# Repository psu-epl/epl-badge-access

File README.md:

# epl-badge-access

This is a mono-repo that contains hardwire designs, software, and documentation for a complete dual-band RFID access control system. This repo represents the work produced by ECE capstone team 17 during the 2021 - 2022 academic year.

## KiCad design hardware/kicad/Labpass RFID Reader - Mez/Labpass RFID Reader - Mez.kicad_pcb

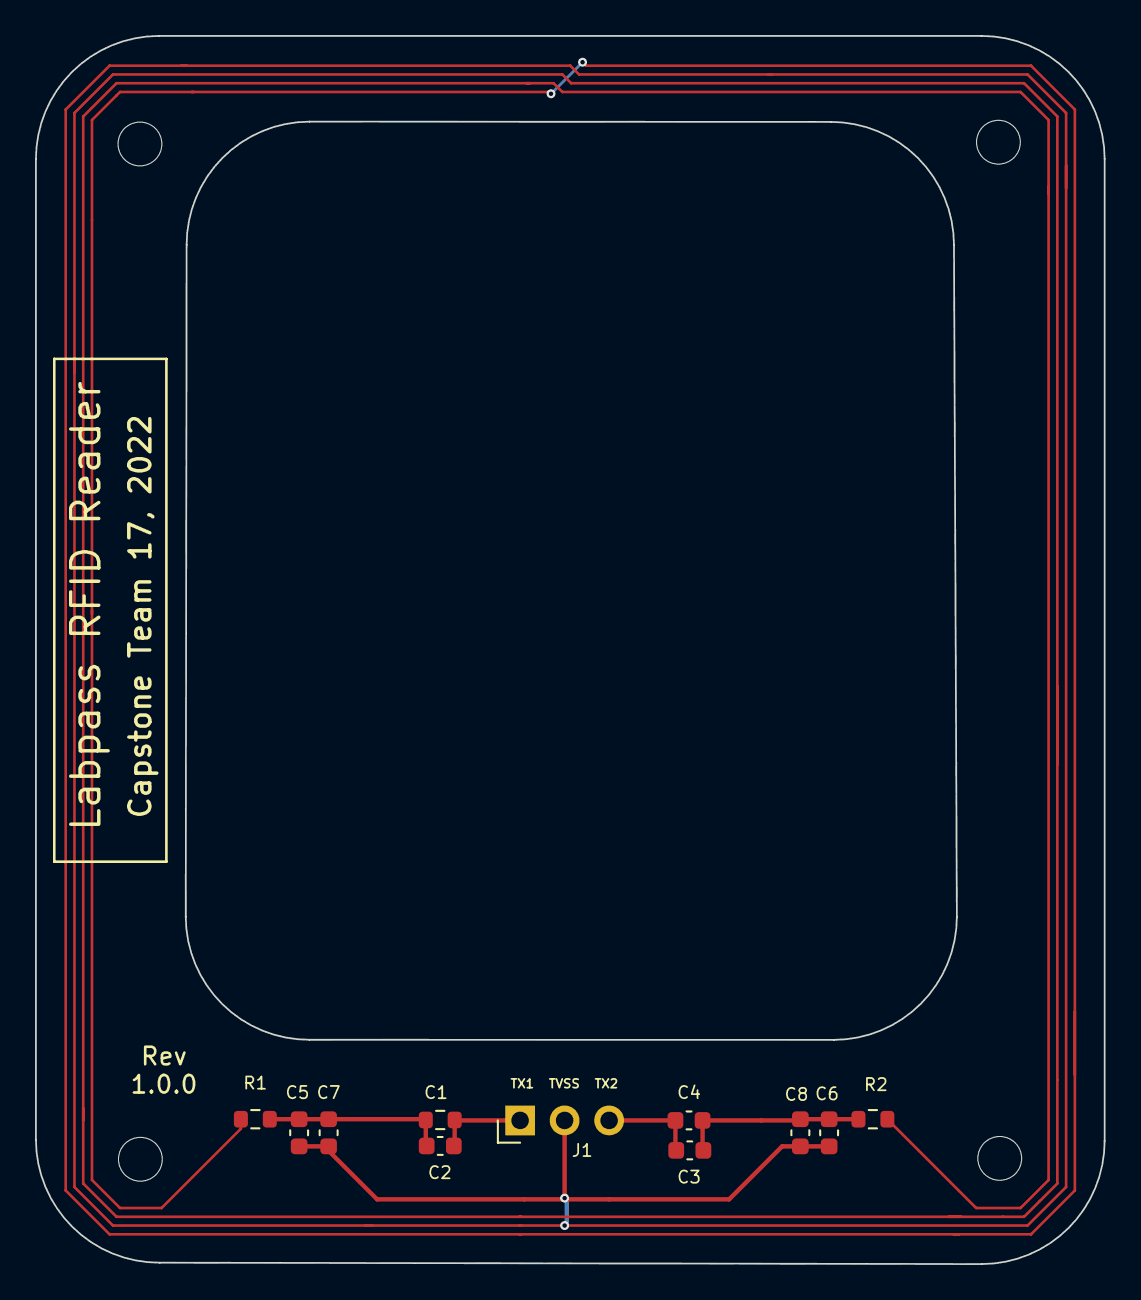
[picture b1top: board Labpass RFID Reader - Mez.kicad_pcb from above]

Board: 2 copper layers, 61.0 x 70.1 mm, 11 parts (0 on the bottom side), 5 nets.

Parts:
C1: 11p; R_0603_1608Metric
C2, C3: NC; C_0603_1608Metric
C4: 11p; C_0603_1608Metric
C5, C6: 30p; C_0603_1608Metric
C7, C8: 32p; C_0603_1608Metric
J1: Conn_01x03_Male; PinHeader_1x03_P2.54mm_Horizontal
R1, R2: R_US; R_0603_1608Metric

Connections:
unnamed: C1.1, C2.1, J1.1
unnamed: C1.2, C2.2, C5.2, C7.1, R1.1
unnamed: C3.1, C4.1, J1.3
unnamed: C3.2, C4.2, C6.1, C8.2, R2.1
unnamed: C5.1, C6.2, C7.2, C8.1, J1.2, R1.2, R2.2

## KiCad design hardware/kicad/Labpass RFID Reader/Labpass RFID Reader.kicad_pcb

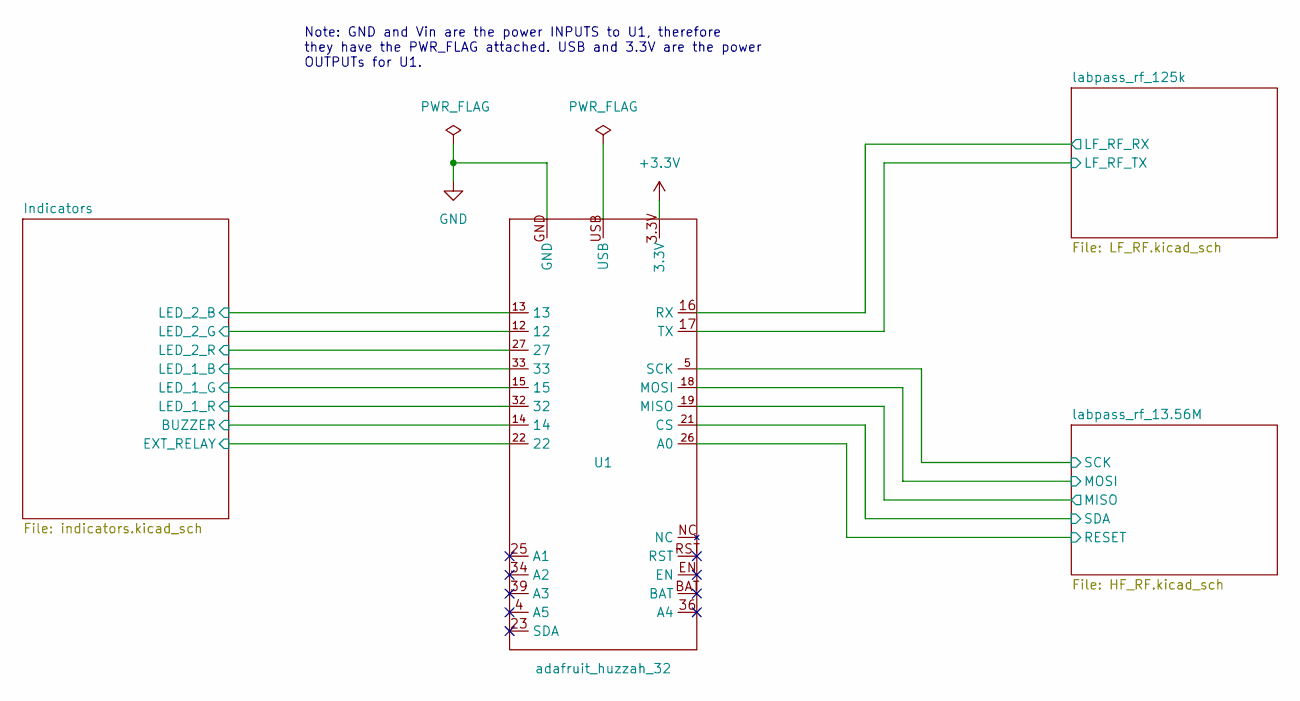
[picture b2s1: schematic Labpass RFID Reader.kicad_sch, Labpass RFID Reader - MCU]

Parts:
U1: adafruit_huzzah_32

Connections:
/Indicators/BUZZER: U1.14; also elsewhere on the board
/Indicators/EXT_RELAY: U1.22; also elsewhere on the board
/Indicators/LED_1_B: U1.33; also elsewhere on the board
/Indicators/LED_1_G: U1.15; also elsewhere on the board
/Indicators/LED_1_R: U1.32; also elsewhere on the board
/Indicators/LED_2_B: U1.13; also elsewhere on the board
/Indicators/LED_2_G: U1.12; also elsewhere on the board
/Indicators/LED_2_R: U1.27; also elsewhere on the board
/labpass_rf_13.56M/MISO: U1.19 (MISO); also elsewhere on the board
/labpass_rf_13.56M/MOSI: U1.18 (MOSI); also elsewhere on the board
/labpass_rf_13.56M/RESET: U1.26 (A0); also elsewhere on the board
/labpass_rf_13.56M/SCK: U1.5 (SCK); also elsewhere on the board
/labpass_rf_13.56M/SDA: U1.21 (CS); also elsewhere on the board
/labpass_rf_125k/LF_RF_RX: U1.16 (RX); also elsewhere on the board
/labpass_rf_125k/LF_RF_TX: U1.17 (TX); also elsewhere on the board

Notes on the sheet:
Note: GND and Vin are the power INPUTS to U1, therefore they have the PWR_FLAG attached. USB and 3.3V are the power OUTPUTs for U1.

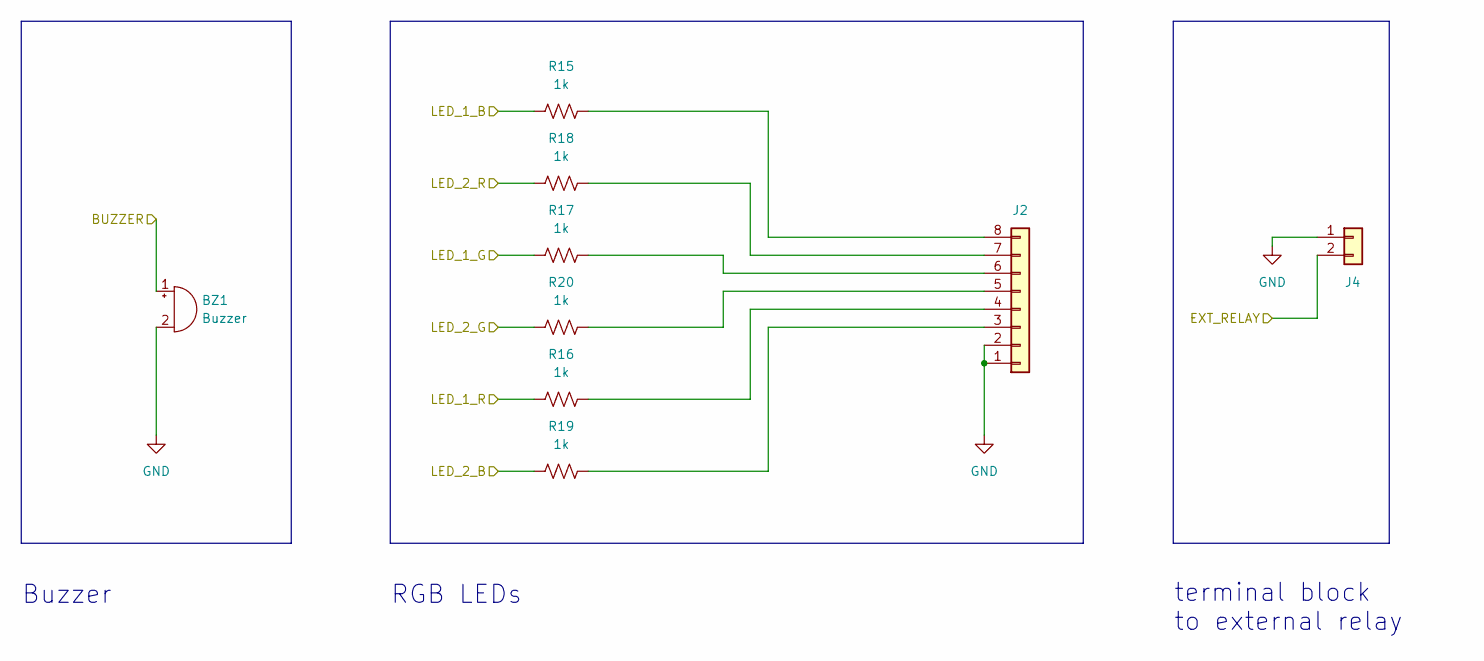
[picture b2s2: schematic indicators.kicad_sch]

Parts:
BZ1: Buzzer; buzzer
J2: Conn_01x08; PinHeader_2x04_P2.54mm_Horizontal
J4: Conn_01x02; Anytek NQ
R15, R16, R17, R18, R19, R20: 1k; R_0603_1608Metric

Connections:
/Indicators/BUZZER: BZ1.1 (-); also elsewhere on the board
/Indicators/EXT_RELAY: J4.2; also elsewhere on the board
/Indicators/LED_1_B: R15.1; also elsewhere on the board
/Indicators/LED_1_G: R17.1; also elsewhere on the board
/Indicators/LED_1_R: R16.1; also elsewhere on the board
/Indicators/LED_2_B: R19.1; also elsewhere on the board
/Indicators/LED_2_G: R20.1; also elsewhere on the board
/Indicators/LED_2_R: R18.1; also elsewhere on the board
unnamed: J2.3, R19.2
unnamed: J2.4, R16.2
unnamed: J2.5, R20.2
unnamed: J2.6, R17.2
unnamed: J2.7, R18.2
unnamed: J2.8, R15.2

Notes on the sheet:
RGB LEDs
terminal block to external relay
Buzzer

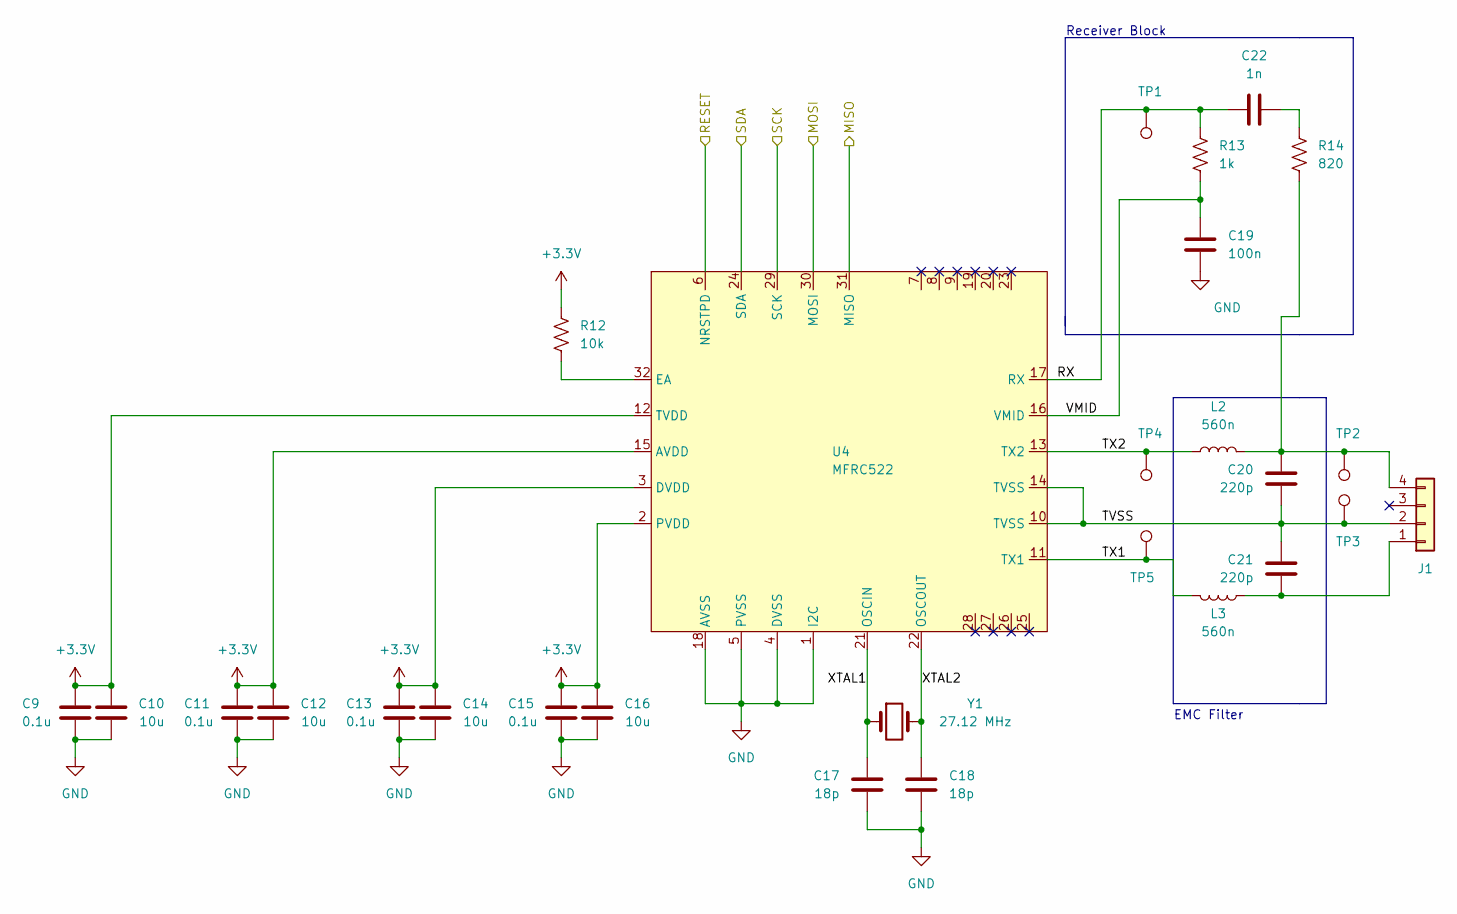
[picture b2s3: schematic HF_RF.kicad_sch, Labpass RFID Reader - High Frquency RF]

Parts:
C9, C11, C13, C15: 0.1u; C_0603_1608Metric
C10, C12, C14, C16: 10u; C_0603_1608Metric
C17, C18: 18p; C_0603_1608Metric
C19: 100n; C_0603_1608Metric
C20, C21: 220p; C_0603_1608Metric
C22: 1n; C_0603_1608Metric
J1: (no value)
L2, L3: 560n; L_1210_3225Metric
R12: 10k; R_0603_1608Metric
R13: 1k; R_0603_1608Metric
R14: 820; R_0603_1608Metric
TP1, TP2, TP3, TP4, TP5: TestPoint; TestPoint_Pad_1.0x1.0mm
U4: MFRC522; LQFP-32_5x5mm_P0.5mm
Y1: 27.12 MHz; Crystal_SMD_5032-2Pin_5.0x3.2mm

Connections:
/labpass_rf_13.56M/MISO: U4.31 (MISO); also elsewhere on the board
/labpass_rf_13.56M/MOSI: U4.30 (MOSI); also elsewhere on the board
/labpass_rf_13.56M/RESET: U4.6 (NRSTPD); also elsewhere on the board
/labpass_rf_13.56M/RX: C22.1, R13.1, TP1.1, U4.17 (RX)
/labpass_rf_13.56M/SCK: U4.29 (SCK); also elsewhere on the board
/labpass_rf_13.56M/SDA: U4.24 (SDA); also elsewhere on the board
/labpass_rf_13.56M/TVSS: C20.1, C21.2, J1.2, TP3.1, U4.10 (TVSS), U4.14 (TVSS)
/labpass_rf_13.56M/TX1: L3.2, TP5.1, U4.11 (TX1)
/labpass_rf_13.56M/TX2: L2.1, TP4.1, U4.13 (TX2)
/labpass_rf_13.56M/VMID: C19.1, R13.2, U4.16 (VMID)
/labpass_rf_13.56M/XTAL1: C17.2, U4.21 (OSCIN), Y1.1
/labpass_rf_13.56M/XTAL2: C18.1, U4.22 (OSCOUT), Y1.2
unnamed: C20.2, J1.4, L2.2, R14.1, TP2.1
unnamed: C21.1, J1.1, L3.1
unnamed: C22.2, R14.2
unnamed: R12.2, U4.32 (EA)

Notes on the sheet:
Receiver Block
EMC Filter

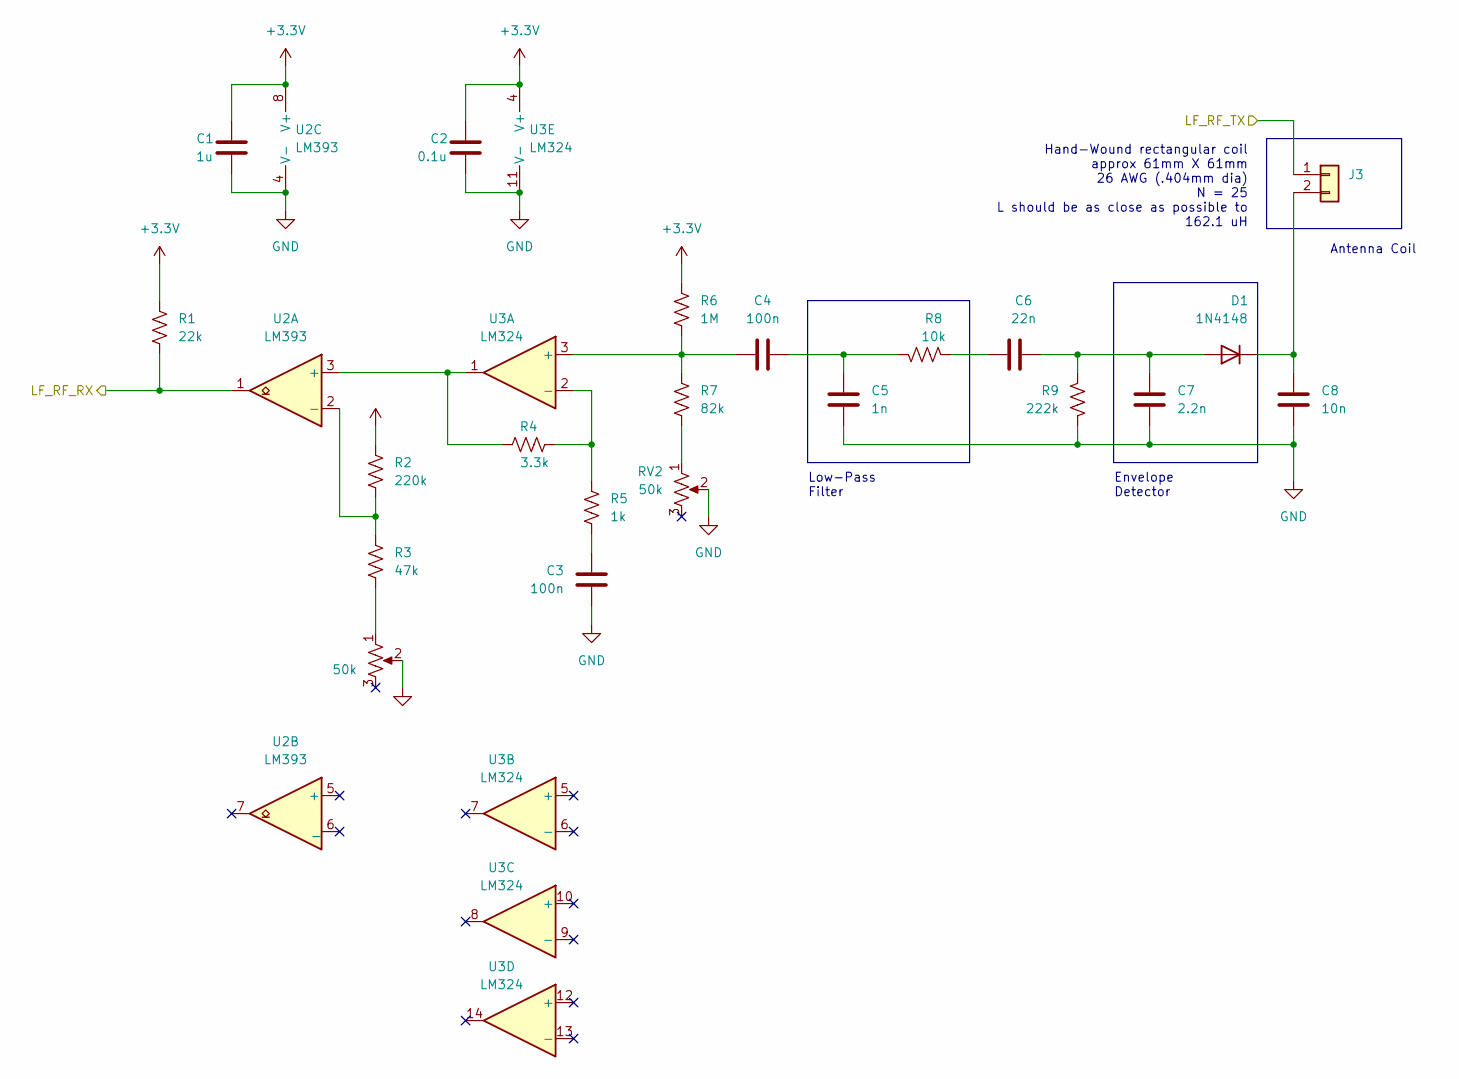
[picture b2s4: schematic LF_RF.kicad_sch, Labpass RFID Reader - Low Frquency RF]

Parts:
C1: 1u; C_0603_1608Metric
C2: 0.1u; C_0603_1608Metric
C3, C4: 100n; C_0603_1608Metric
C5: 1n; C_0603_1608Metric
C6: 22n; C_0603_1608Metric
C7: 2.2n; C_0603_1608Metric
C8: 10n; C_0603_1608Metric
D1: 1N4148; D_SOD-323F
J3: Conn_01x02; PinHeader_1x02_P2.54mm_Horizontal
R1: 22k; R_0603_1608Metric
R2: 220k; R_0603_1608Metric
R3: 47k; R_0603_1608Metric
R4: 3.3k; R_0603_1608Metric
R5: 1k; R_0603_1608Metric
R6: 1M; R_0603_1608Metric
R7: 82k; R_0603_1608Metric
R8: 10k; R_0603_1608Metric
R9: 222k; R_0603_1608Metric
RV1, RV2: 50k; TC33X
U2: LM393; SOIC-8_3.9x4.9mm_P1.27mm
U3: LM324; SO-14_3.9x8.65mm_P1.27mm

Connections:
/labpass_rf_125k/LF_RF_RX: R1.2, U2.1; also elsewhere on the board
/labpass_rf_125k/LF_RF_TX: J3.1; also elsewhere on the board
unnamed: C3.2, R5.2
unnamed: C4.1, R6.2, R7.1, U3.3 (+)
unnamed: C4.2, C5.1, R8.1
unnamed: C6.1, C7.1, D1.2 (A), R9.2
unnamed: C6.2, R8.2
unnamed: C8.1, D1.1 (K), J3.2
unnamed: R2.2, R3.1, U2.2 (-)
unnamed: R3.2, RV1.1
unnamed: R4.1, R5.1, U3.2 (-)
unnamed: R4.2, U2.3 (+), U3.1
unnamed: R7.2, RV2.1

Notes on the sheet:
Hand-Wound rectangular coil approx 61mm X 61mm 26 AWG (.404mm dia) N = 25 L should be as close as possible to 162.1 uH
Antenna Coil
Envelope Detector
Low-Pass Filter

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
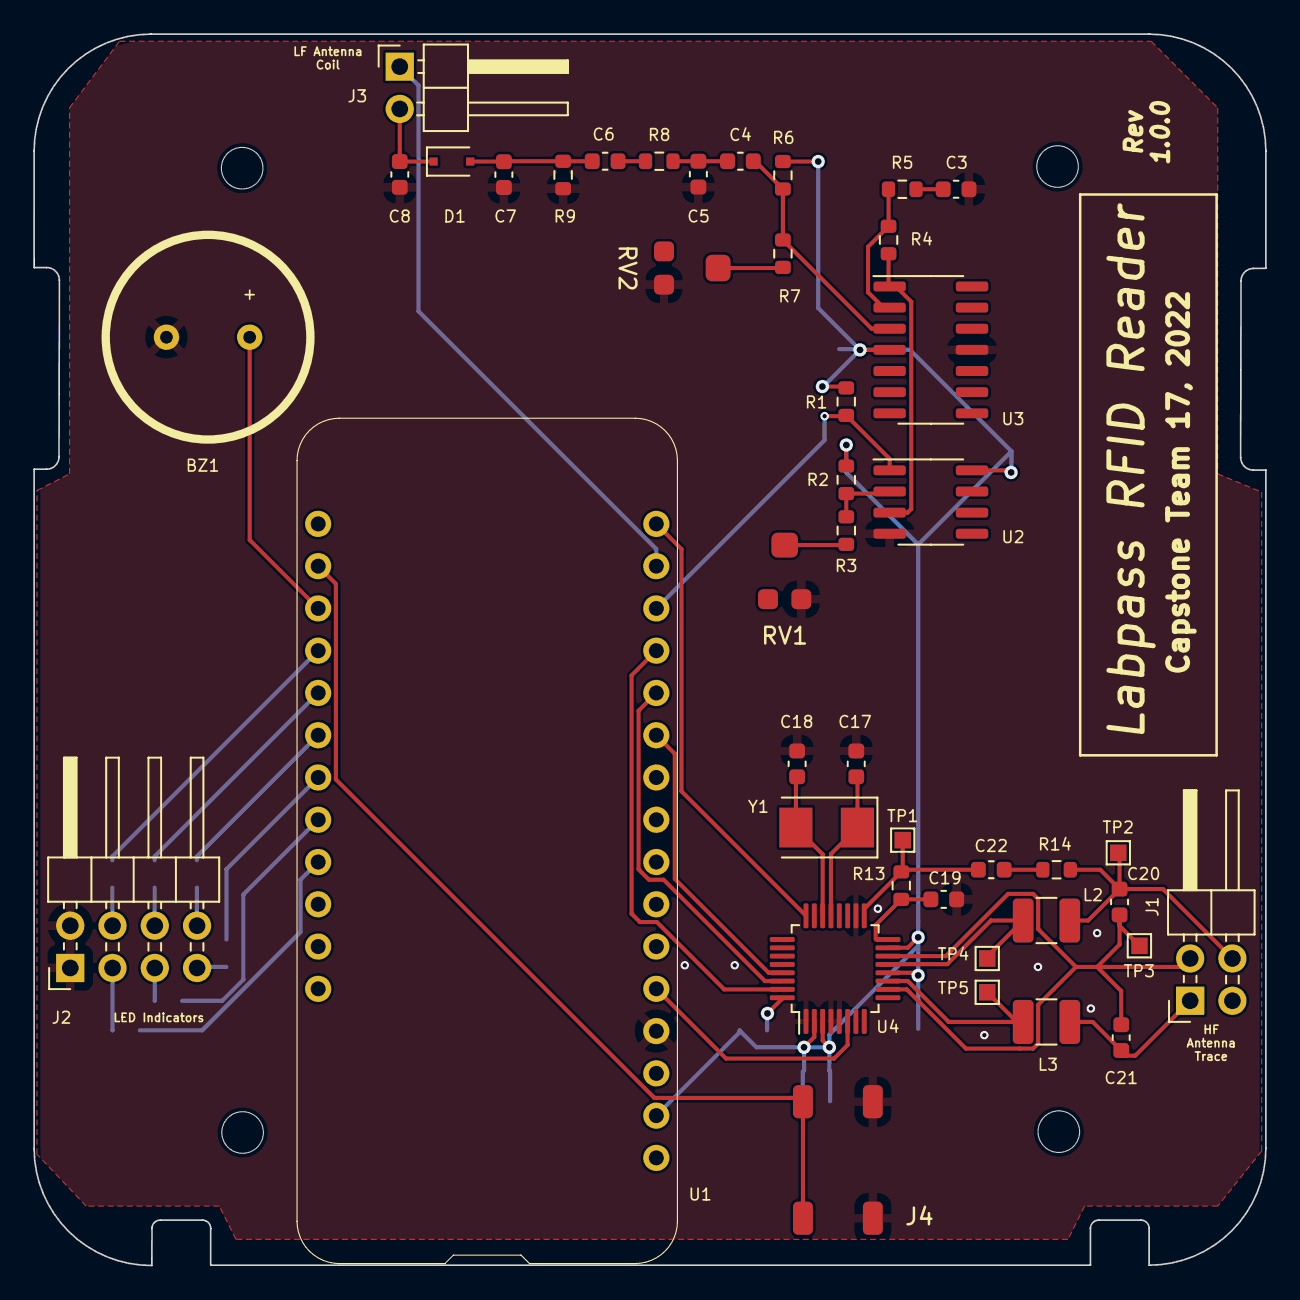
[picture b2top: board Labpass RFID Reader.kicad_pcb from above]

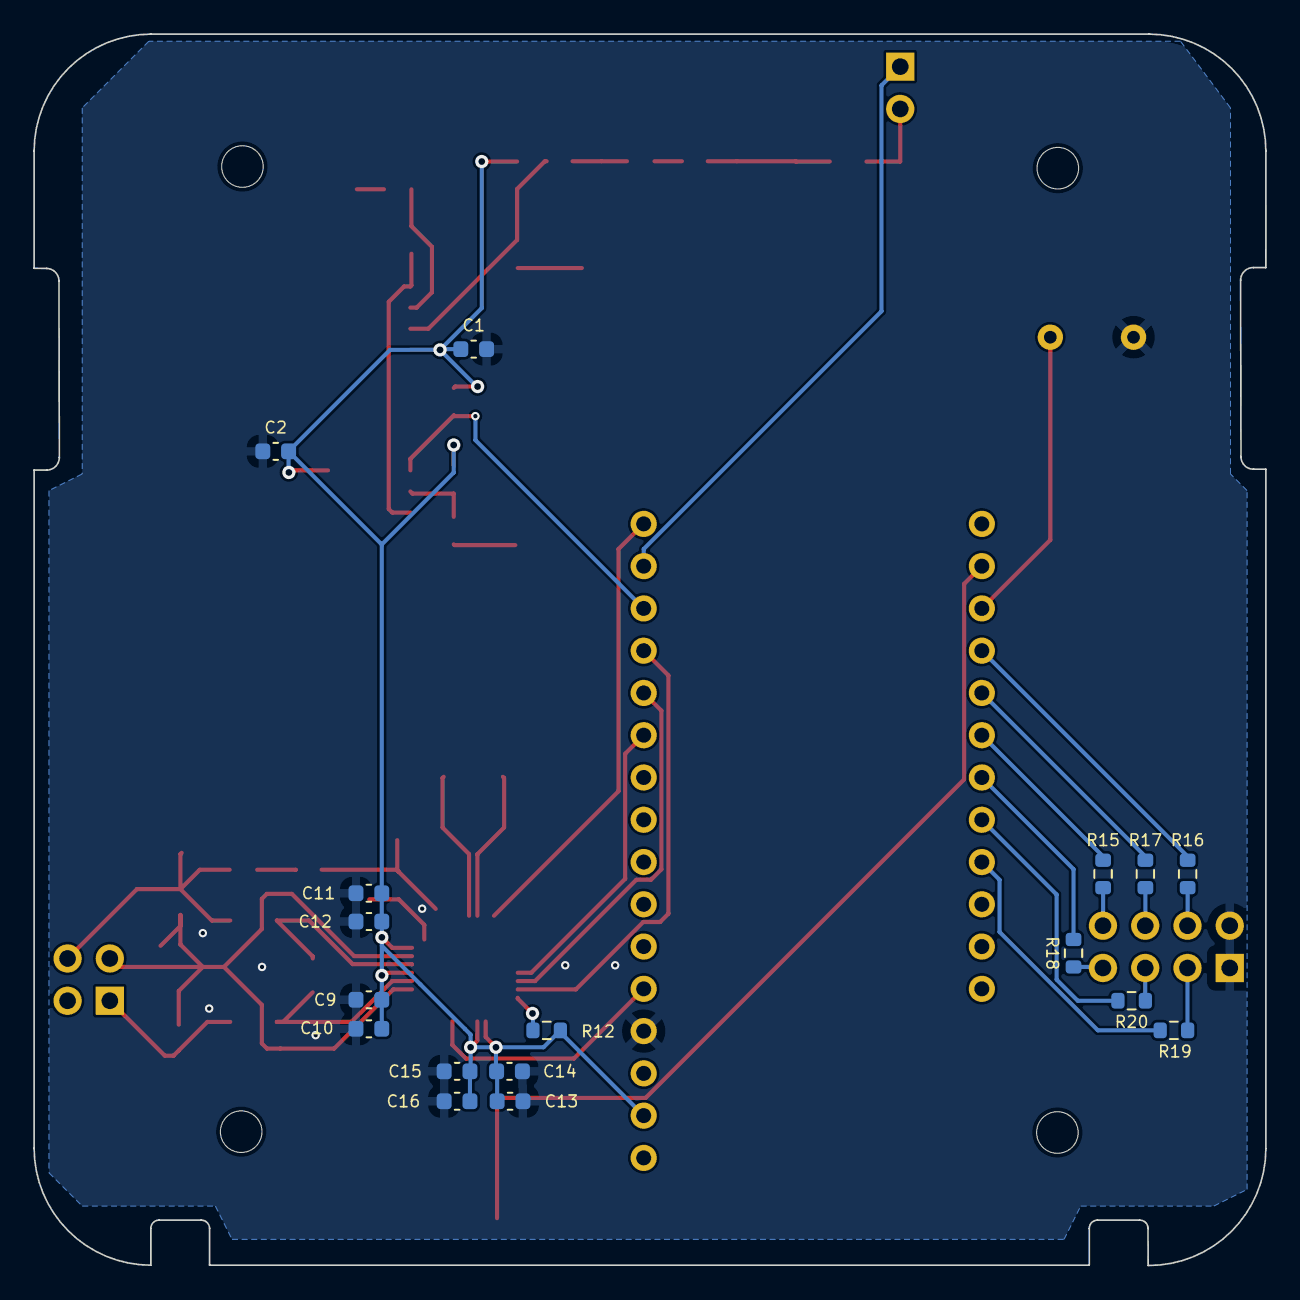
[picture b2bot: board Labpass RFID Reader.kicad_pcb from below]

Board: 2 copper layers, 74.0 x 74.0 mm, 60 parts (17 on the bottom side), 45 nets.

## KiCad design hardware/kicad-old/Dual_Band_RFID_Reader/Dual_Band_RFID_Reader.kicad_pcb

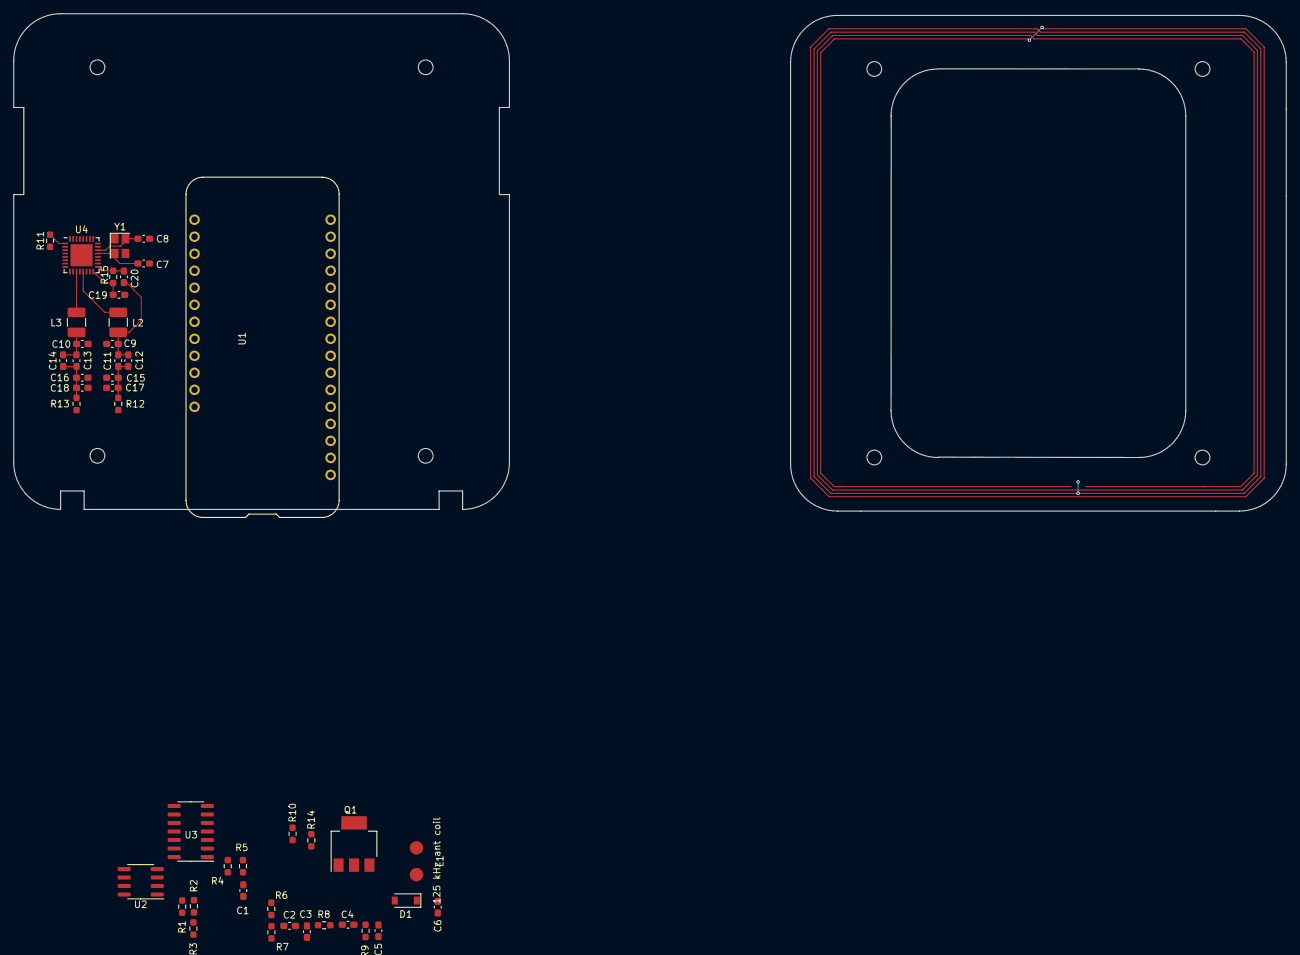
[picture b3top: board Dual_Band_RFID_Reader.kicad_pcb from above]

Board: 2 copper layers, 45 parts (0 on the bottom side), 34 nets.

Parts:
C1, C2: 100 nF; C_0603_1608Metric_Pad1.08x0.95mm_HandSolder
C3: 1 nF; C_0603_1608Metric_Pad1.08x0.95mm_HandSolder
C4: 22 nF; C_0603_1608Metric_Pad1.08x0.95mm_HandSolder
C5: 2.2 nF; C_0603_1608Metric_Pad1.08x0.95mm_HandSolder
C6: 10n; C_0603_1608Metric_Pad1.08x0.95mm_HandSolder
C7, C8, C9, C10, C11, C12, C13, C14, C15, C16, C17, C18, C19, C20: C; C_0603_1608Metric_Pad1.08x0.95mm_HandSolder
D1: 1N4148; D_SOD-123
L1: 162 µH; LF Antenna Pads
L2, L3: INDUCTOR; L_1210_3225Metric_Pad1.42x2.65mm_HandSolder
Q1: BC517; SOT-223
R1: 22 kΩ; R_0603_1608Metric_Pad0.98x0.95mm_HandSolder
R2: 330 kΩ; R_0603_1608Metric_Pad0.98x0.95mm_HandSolder
R3: 120 kΩ; R_0603_1608Metric_Pad0.98x0.95mm_HandSolder
R4: 3.3 kΩ; R_0603_1608Metric_Pad0.98x0.95mm_HandSolder
R5, R10: 1 kΩ; R_0603_1608Metric_Pad0.98x0.95mm_HandSolder
R6: 1 MΩ; R_0603_1608Metric_Pad0.98x0.95mm_HandSolder
R7: 100 kΩ; R_0603_1608Metric_Pad0.98x0.95mm_HandSolder
R8: 10 kΩ; R_0603_1608Metric_Pad0.98x0.95mm_HandSolder
R9: 267 kΩ; R_0603_1608Metric_Pad0.98x0.95mm_HandSolder
R11, R12, R13, R15: 10k; R_0603_1608Metric_Pad0.98x0.95mm_HandSolder
R14: 56Ω; R_0603_1608Metric_Pad0.98x0.95mm_HandSolder
U1: Adafruit_Huzzah32; Adafruit Feather Huzzah 32
U2: LM393; SOIC-8_3.9x4.9mm_P1.27mm
U3: LM324; SOIC-14_3.9x8.7mm_P1.27mm
U4: MFRC522; QFN-32-1EP_5x5mm_P0.5mm_EP3.3x3.3mm
Y1: Crystal; Crystal_SMD_3225-4Pin_3.2x2.5mm_HandSoldering

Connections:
+3V3: R1.1, R2.1, R6.1, R11.1, U1.2 (3.3V), U4.2 (PVDD), U4.3 (DVDD), U4.12 (TVDD), U4.15 (AVDD)
+5V: R14.1, U1.26 (USB)
/High Frequency RF/CS: U1.16 (CS), U4.24 (SDA)
/High Frequency RF/MISO: U1.13 (MISO), U4.31 (MISO)
/High Frequency RF/MOSI: U1.12 (MOSI), U4.30 (MOSI)
/High Frequency RF/RST: U1.23 (RST), U4.6 (NRSTPD)
/High Frequency RF/SCK: U1.11 (SCK), U4.29 (SCK)
/Low Frequency RF/LF_RF_RX: R1.2, U1.14 (RX), U2.1
/Low Frequency RF/LF_RF_TX: R10.2, U1.15 (TX)
GND: C1.1, C3.1, C5.2, C6.2, C7.2, C8.2, C19.2, R3.2, R7.2, R9.2, U1.4 (GND), U4.4 (DVSS), U4.5 (PVSS), U4.14 (TVSS), U4.18 (AVSS), U4.32 (EA)
unnamed: C1.2, R5.1
unnamed: C2.2, C3.2, R8.1
unnamed: C4.1, R8.2
unnamed: C10.2, C13.2, C14.2, L3.2
unnamed: C11.1, C12.1, C15.2, C17.2, R12.2
unnamed: C9.1, C11.2, C12.2, C20.1, L2.2
unnamed: C13.1, C14.1, C16.1, C18.1, R13.2
unnamed: C4.2, C5.1, D1.2 (A), R9.1
unnamed: C6.1, D1.1 (K), L1.1
unnamed: Q1.2 (B), R10.1
unnamed: Q1.1 (C), R14.2
unnamed: L1.2, Q1.3 (E)
unnamed: R4.1, U2.3 (+), U3.1
unnamed: R2.2, R3.1, U2.2 (-)
unnamed: C2.1, R6.2, R7.1, U3.3 (+)
unnamed: R4.2, R5.2, U3.2 (-)
unnamed: R11.2, U4.1 (I2C)
unnamed: C7.1, U4.21 (OSCIN), Y1.3
unnamed: C8.1, U4.22 (OSCOUT), Y1.1
unnamed: C20.2, R15.2, U4.17 (RX)
unnamed: C9.2, C10.1, C15.1, C16.2, C17.1, C18.2, R12.1, R13.1, U4.10 (TVSS)
unnamed: L3.1, U4.11 (TX1)
unnamed: L2.1, U4.13 (TX2)
unnamed: C19.1, R15.1, U4.16 (VMID)

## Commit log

2022-02-21 Initial commit of 125k hardware + software design
    Note: Documentation included separately using the github
    wiki located at:
    https://github.com/psu-epl/epl-badge-access/wiki
    * Working 125k rfid reader circuit schematic captures in kicad
    * LF antenna VNA analysis
    * Relevant datasheets
2022-02-22 Add the full PlatformIO directory for the reader software
    See the README for a complete explanation, but this is a complete
    codebase for an embedded system using Visual Studio Code along
    with the PlatformIO extension.
    This is a much nicer exaperience than using the Arduino IDE.
2022-03-07 Add HF and LF analog RF drivers
2022-03-07 Antenna files
    The NXP design doc AN1445 (Antenna design for MFRC522) contains
    the recommended impedance matching circuitry and calculations. NXP
    makes an excel spreadsheet available to make the calculations a
    little easier, but I refuse to use excel so here we are.
    I made a matlab script to do the calc necessar for the HF impedance
    matching.
2022-03-07 First pass at HF and LF schematics
2022-03-09 * Move task spawn into RF classes * consolidate threading; HF doesn't need two
2022-03-14 move sheet template to kicad project folder
2022-03-14 Reader tweaks for 125k
2022-03-14 Remove IRQ hw line from MFRC522, it's not useful
2022-04-02 adding Mousa's board work to branch
2022-04-03 Board Layout WIP
    * Added correct footprint for the components that were
    producing errors
    * added HF antenna trace on board periphery
    * added pads for the LF antenna coil to be connected later
    * corrected all the DRC errors
    * completed HF layout
2022-04-15 PCB Check
2022-04-16 Updates traces
2022-04-16 Updates traces_1
2022-04-16 Update traces_2
2022-04-16 Update traces_3
2022-04-17 Re-do kicad all ki-cad files using 6.04 stable *sigh*
2022-04-18 Re-do board design using kicad 6.04 stable
2022-04-19 Polish reposition pin headers to clear mez board
2022-04-20 Add RGB LEDs with 4 wires
2022-04-23 last-minute fixes
2022-04-23 fix ansible for provisioning
2022-04-24 first pass
2022-04-25 move secrets to out-of-band delivery
2022-04-25 Add temp seed container
2022-04-25 Tweaks
2022-04-25 more tweaks
2022-04-25 Remove seed from ansible, run from user-data
2022-04-26 kicad backups
2022-04-26 Create CAD
2022-05-07 buzzer, RGBled, wifiClient
2022-05-07 Added default_state
2022-05-10 add missing dc blocking cap to HF path
2022-05-10 Several fixes
    * EA and I2C were backwards
    * Adding missing Crx into HF receive path
    * Better header size and placement
2022-05-15 Additional Changes
    * remove transistor on LF path and power coil directly
    from ESP TX pin at 3.3V
    * add some test points around the HF path
    * add some cheap pots on LF for tuning the amplifier bias
    and comparator threshold
2022-05-16 temp
2022-05-16 Add terminal block for gpio to ext relay
2022-05-16 bump rev to 1.0.0
2022-05-16 Add back the mounting holes
2022-05-18 tweak incorrect designation for jumper
2022-05-18 More
2022-05-18 more_1
2022-05-18 wip reader
2022-05-20 From Wednesday 05/18/2022 meeting
2022-05-26 add some text to the fab layer for placement
2022-05-26 Refine the state machine for reader
2022-06-03 more temp
2022-06-10 Final rev 1.0.0
2022-06-10 Final Firmware
2022-06-10 Add final labpass server
